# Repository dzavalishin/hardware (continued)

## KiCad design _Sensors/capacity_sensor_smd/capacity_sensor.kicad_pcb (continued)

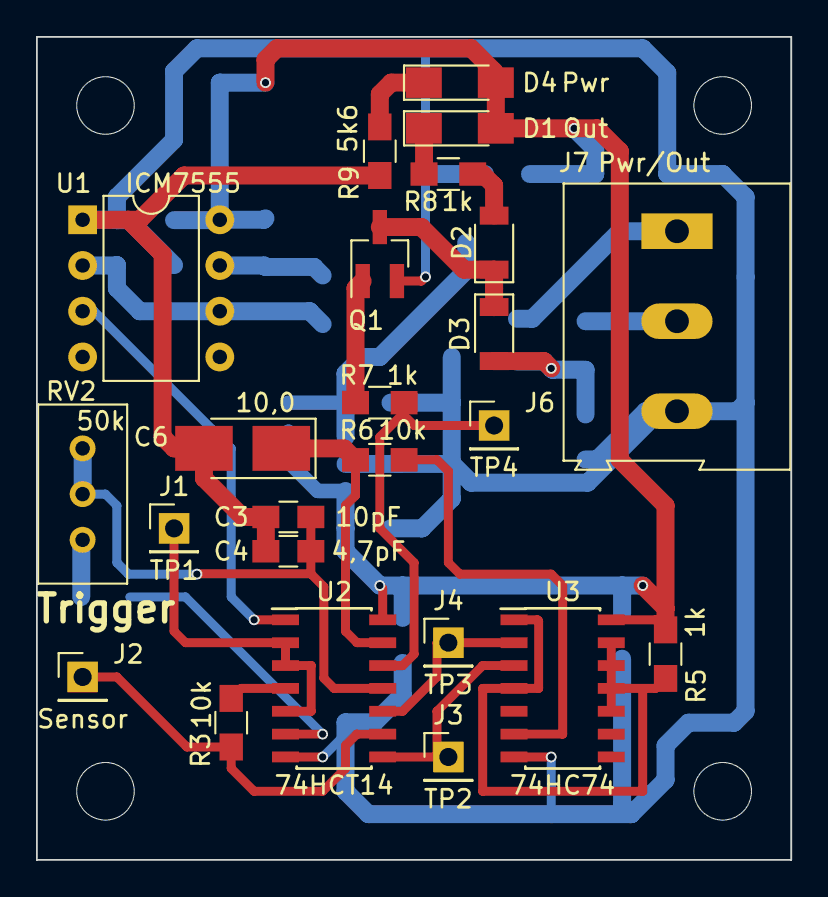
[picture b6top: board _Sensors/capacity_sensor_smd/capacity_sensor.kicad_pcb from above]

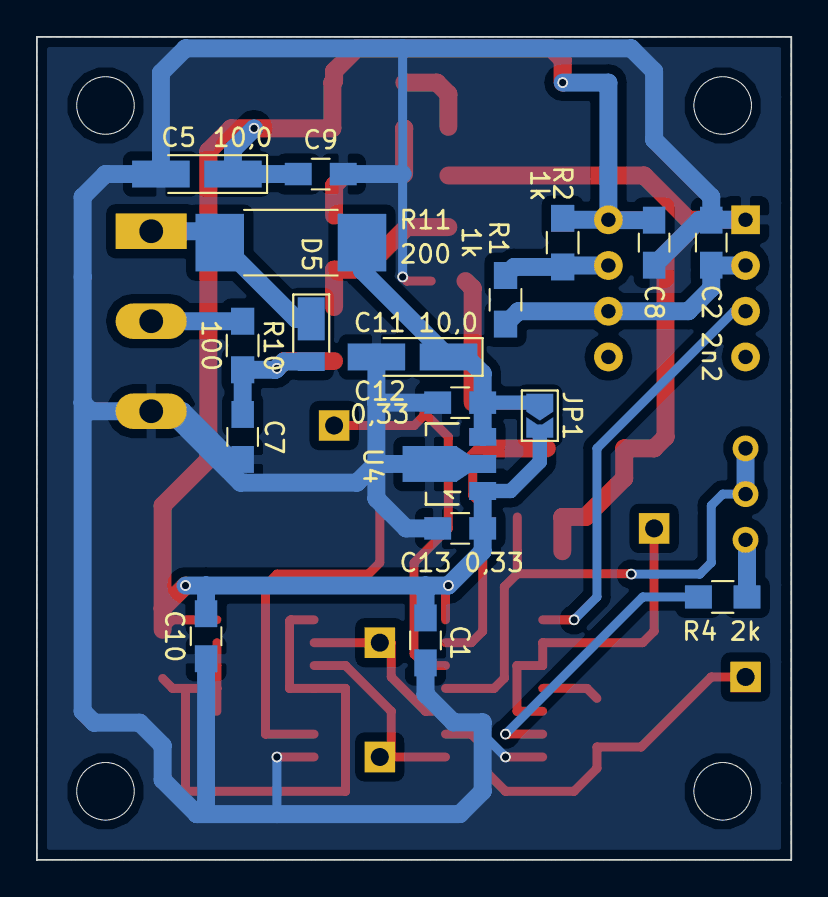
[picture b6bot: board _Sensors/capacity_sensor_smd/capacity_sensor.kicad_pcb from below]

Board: 2 copper layers, 41.9 x 45.7 mm, 46 parts (18 on the bottom side), 26 nets.

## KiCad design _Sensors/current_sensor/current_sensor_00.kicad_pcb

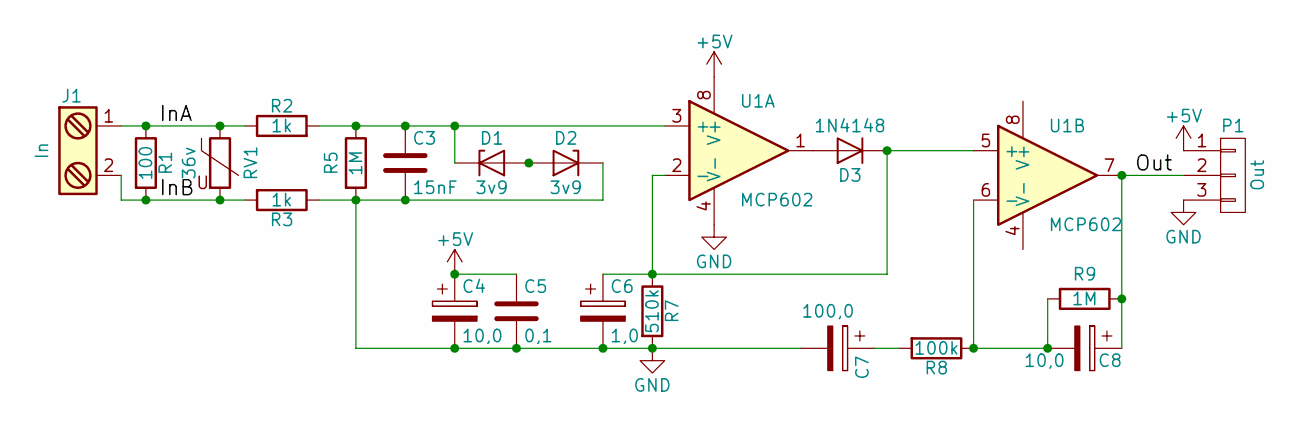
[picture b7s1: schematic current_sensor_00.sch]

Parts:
C3: 15nF; C_1206_HandSoldering
C4, C8: 10,0; C_0805_HandSoldering
C5: 0,1; C_1206_HandSoldering
C6: 1,0; C_0805_HandSoldering
C7: 100,0; CP_Elec_6.3x5.7
D1, D2: 3v9; D_MiniMELF_Handsoldering
D3: 1N4148; D_MiniMELF_Handsoldering
J1: In; TerminalBlock_Pheonix_MKDS1.5-2pol
P1: Out; Socket_Strip_Angled_1x03
R1: 100; R_Axial_DIN0516_L15.5mm_D5.0mm_P20.32mm_Horizontal
R2, R3: 1k; R_1206_HandSoldering
R5, R9: 1M; R_1206_HandSoldering
R7: 510k; R_1206_HandSoldering
R8: 100k; R_1206_HandSoldering
RV1: 36v; RV_Disc_D7_W5.1_P5
U1: MCP602; DIP-8_W7.62mm_Socket_LongPads

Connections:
+5V: C4.1, C5.1, P1.1, U1.8 (V+)
/InA: J1.1, R1.1, R2.1, RV1.1
/InB: J1.2, R1.2, R3.2, RV1.2
/Out: C8.1, P1.2, R9.1, U1.7
GND: C3.2, C4.2, C5.2, C6.2, C7.2, D2.1 (K), P1.3, R3.1, R5.2, R7.2, U1.4 (V-)
unnamed: C3.1, D1.1 (K), R2.2, R5.1, U1.3 (+)
unnamed: C6.1, D3.1 (K), R7.1, U1.2 (-), U1.5 (+)
unnamed: C7.1, R8.2
unnamed: C8.2, R8.1, R9.2, U1.6 (-)
unnamed: D1.2 (A), D2.2 (A)
unnamed: D3.2 (A), U1.1

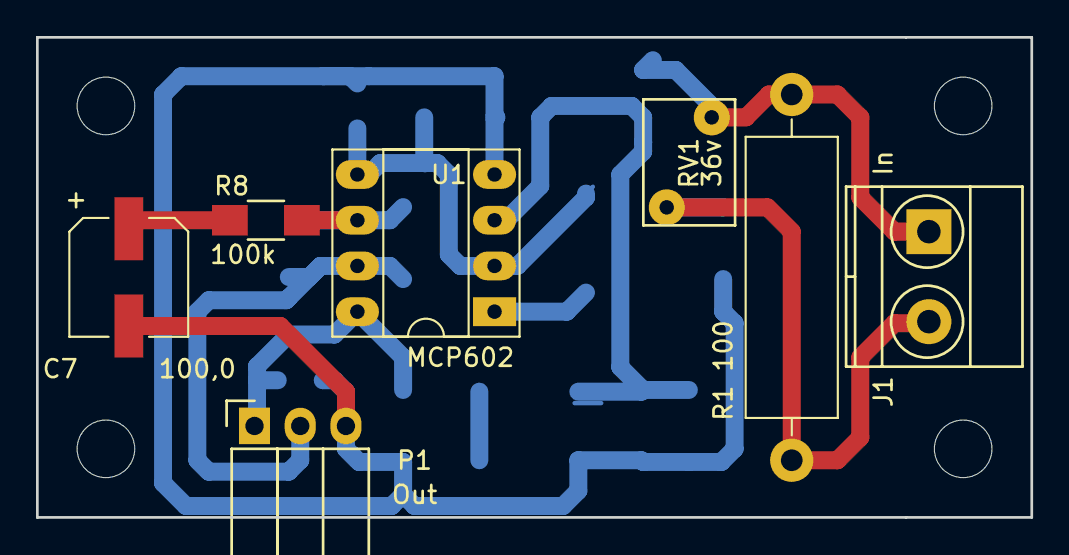
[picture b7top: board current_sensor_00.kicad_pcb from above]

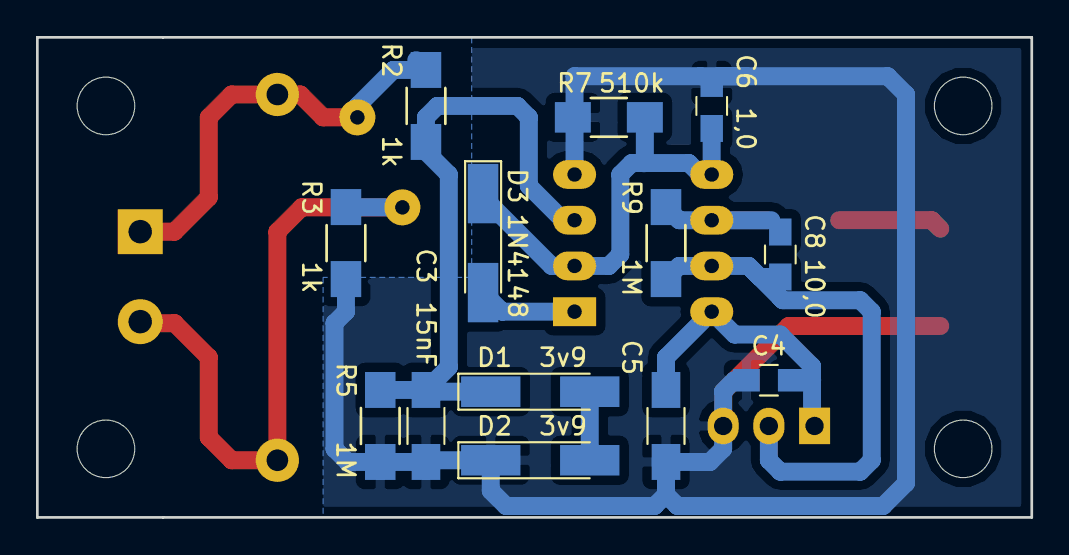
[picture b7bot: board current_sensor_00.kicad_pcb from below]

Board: 2 copper layers, 55.2 x 26.7 mm, 20 parts (13 on the bottom side), 11 nets.

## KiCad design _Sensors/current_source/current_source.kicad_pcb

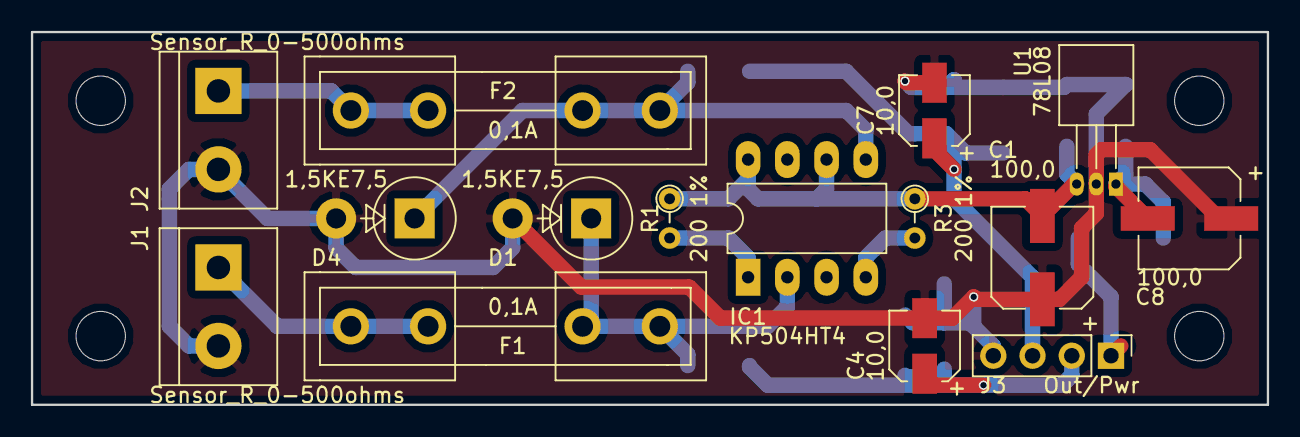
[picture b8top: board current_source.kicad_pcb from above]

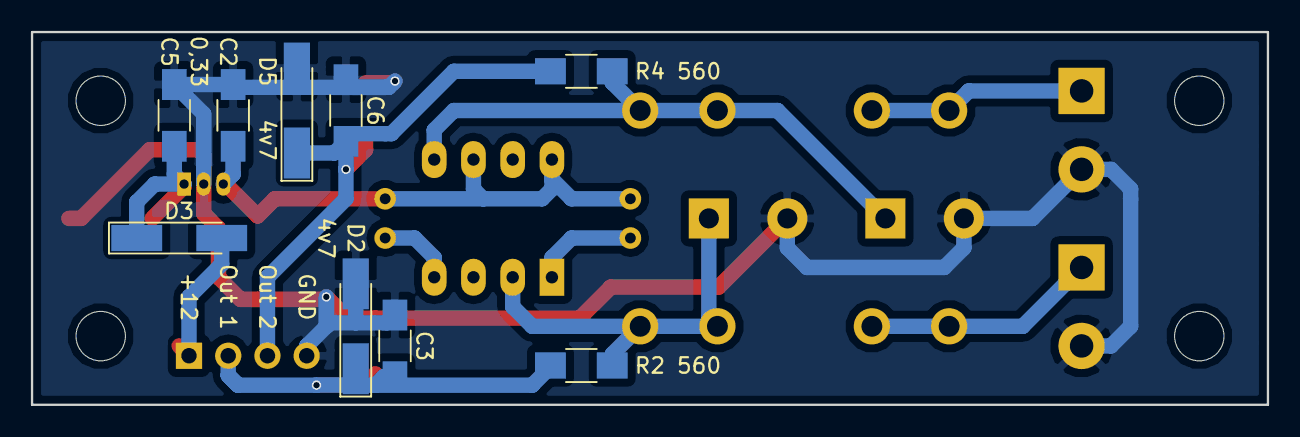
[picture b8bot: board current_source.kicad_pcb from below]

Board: 2 copper layers, 80.0 x 24.1 mm, 24 parts (9 on the bottom side), 12 nets.

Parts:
C1, C8: 100,0; CP_Elec_6.3x5.3
C2, C5: 0,33; C_1206_HandSoldering
C3, C6: 0,1; C_1206_HandSoldering
C4, C7: 10,0; CP_Elec_4x5.7
D1, D4: 1,5KE7,5; D_DO-201_P5.08mm_Vertical_AnodeUp
D2, D5: 4v7; D_MiniMELF_Handsoldering
D3: 1n4148; D_MiniMELF_Handsoldering
F1, F2: 0,1A; Fuseholder5x20_horiz_open_inline_Type-I
IC1: КР504НТ4; DIP-8_W7.62mm_LongPads
J1, J2: Sensor_R_0-500ohms; TerminalBlock_bornier-2_P5.08mm
J3: Out/Pwr; Pin_Header_Straight_1x04_Pitch2.54mm
R1, R3: 200 1%; R_Axial_DIN0204_L3.6mm_D1.6mm_P2.54mm_Vertical
R2, R4: 560; R_1206_HandSoldering
U1: 78L08; TO-92_Horizontal1_Inline_Narrow_Oval

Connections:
+8V: C1.2, C2.1, IC1.6, IC1.8, R1.1, R3.1, U1.3
+12V: D3.2, J3.1
/ADC_In_A: C3.1, C4.1, D2.1, J3.2, R2.1
/ADC_In_B: C6.1, C7.1, D5.1, J3.3, R4.1
GND: C1.1, C2.2, C3.2, C4.2, C5.2, C6.2, C7.2, C8.1, D1.2, D2.2, D4.2, D5.2, J1.2, J2.2, J3.4, U1.2
unnamed: C5.1, C8.2, D3.1, U1.1
unnamed: D1.1, F1.1, IC1.2, R2.2
unnamed: D4.1, F2.1, IC1.5, R4.2
unnamed: F1.2, J1.1
unnamed: F2.2, J2.1
unnamed: IC1.1, R1.2
unnamed: IC1.4, R3.2
